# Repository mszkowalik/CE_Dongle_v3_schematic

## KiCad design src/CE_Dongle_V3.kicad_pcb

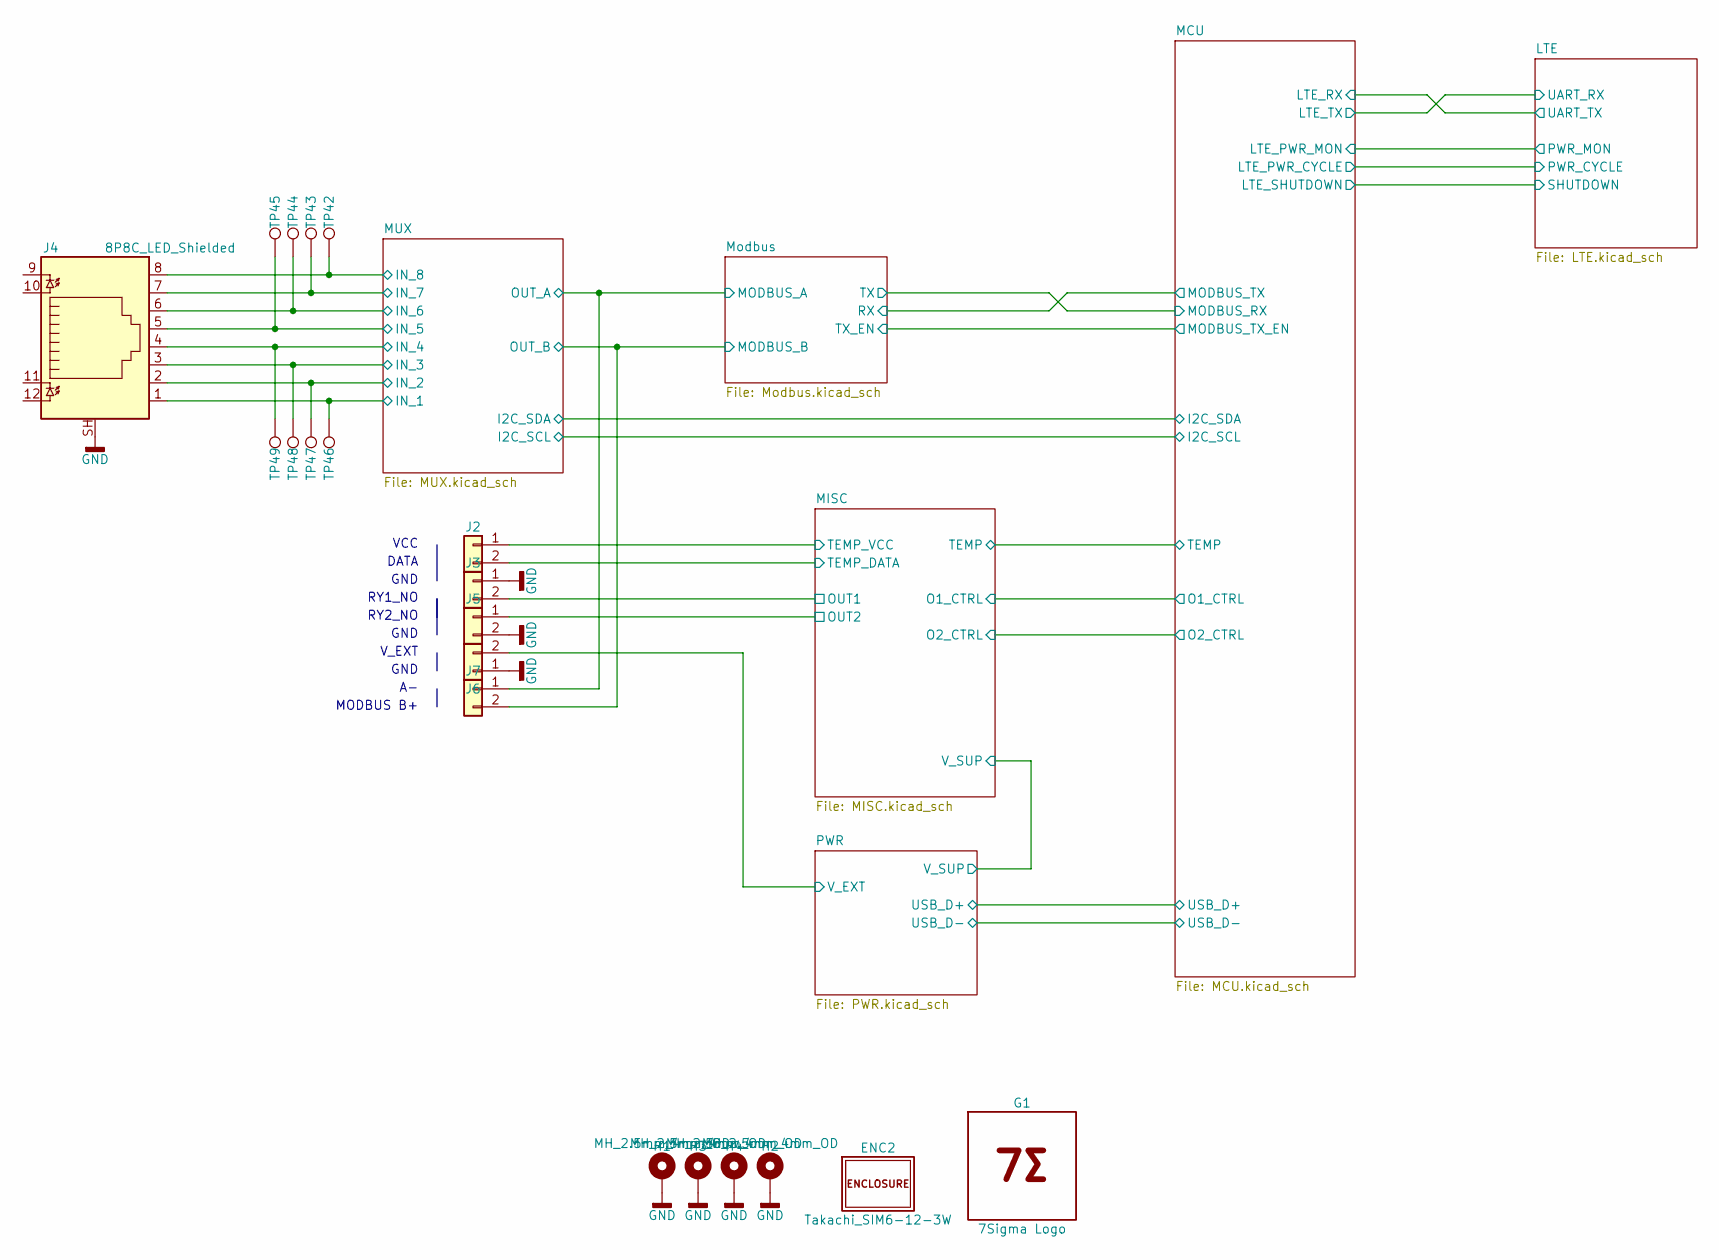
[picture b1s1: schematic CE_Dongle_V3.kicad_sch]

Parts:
ENC2: Takachi_SIM6-12-3W; TAKACHI_SIM6-12-3W; Manufacturer Part Numbe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 SIM6-12-3W
G1: 7Sigma Logo; 7Sigma_Logo
H1, H2, H3, H4: MH_2.5mm_4mm_OD; MountingHole_2.5mm_Pad_4mm
J2, J3, J5, J6, J7: Conn_01x02; CONN-TH_XY302V-3.5-2P; Manufacturer Part Numbe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 XY302V-3.5-2P; LCSC Part C784940
J4: 8P8C_LED_Shielded; RJ45-TH_RC01812; Manufacturer Part Numbe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 RC01812; LCSC Part C708645
TP42, TP43, TP44, TP45, TP46, TP47, TP48, TP49: TestPoint; TestPoint_Pad_D1.5mm

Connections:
/MISC/OUT1: J3.2; also elsewhere on the board
/MISC/OUT2: J5.1; also elsewhere on the board
/MISC/TEMP_DATA: J2.2; also elsewhere on the board
/MISC/TEMP_VCC: J2.1; also elsewhere on the board
/MUX/IN_1: J4.1, TP46.1 (1_1); also elsewhere on the board
/MUX/IN_2: J4.2, TP47.1 (1_1); also elsewhere on the board
/MUX/IN_3: J4.3, TP48.1 (1_1); also elsewhere on the board
/MUX/IN_4: J4.4, TP49.1 (1_1); also elsewhere on the board
/MUX/IN_5: J4.5, TP45.1 (1_1); also elsewhere on the board
/MUX/IN_6: J4.6, TP44.1 (1_1); also elsewhere on the board
/MUX/IN_7: J4.7, TP43.1 (1_1); also elsewhere on the board
/MUX/IN_8: J4.8, TP42.1 (1_1); also elsewhere on the board
/MUX/OUT_A: J7.1; also elsewhere on the board
/MUX/OUT_B: J7.2; also elsewhere on the board
/PWR/V_EXT: J6.2; also elsewhere on the board
GND: H1.1 (1_1), H2.1 (1_1), H3.1 (1_1), H4.1 (1_1), J3.1, J4.SH, J5.2, J6.1; also elsewhere on the board

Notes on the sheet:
VCC
GND
V_EXT
RY1_NO
DATA
MODBUS B+
RY2_NO

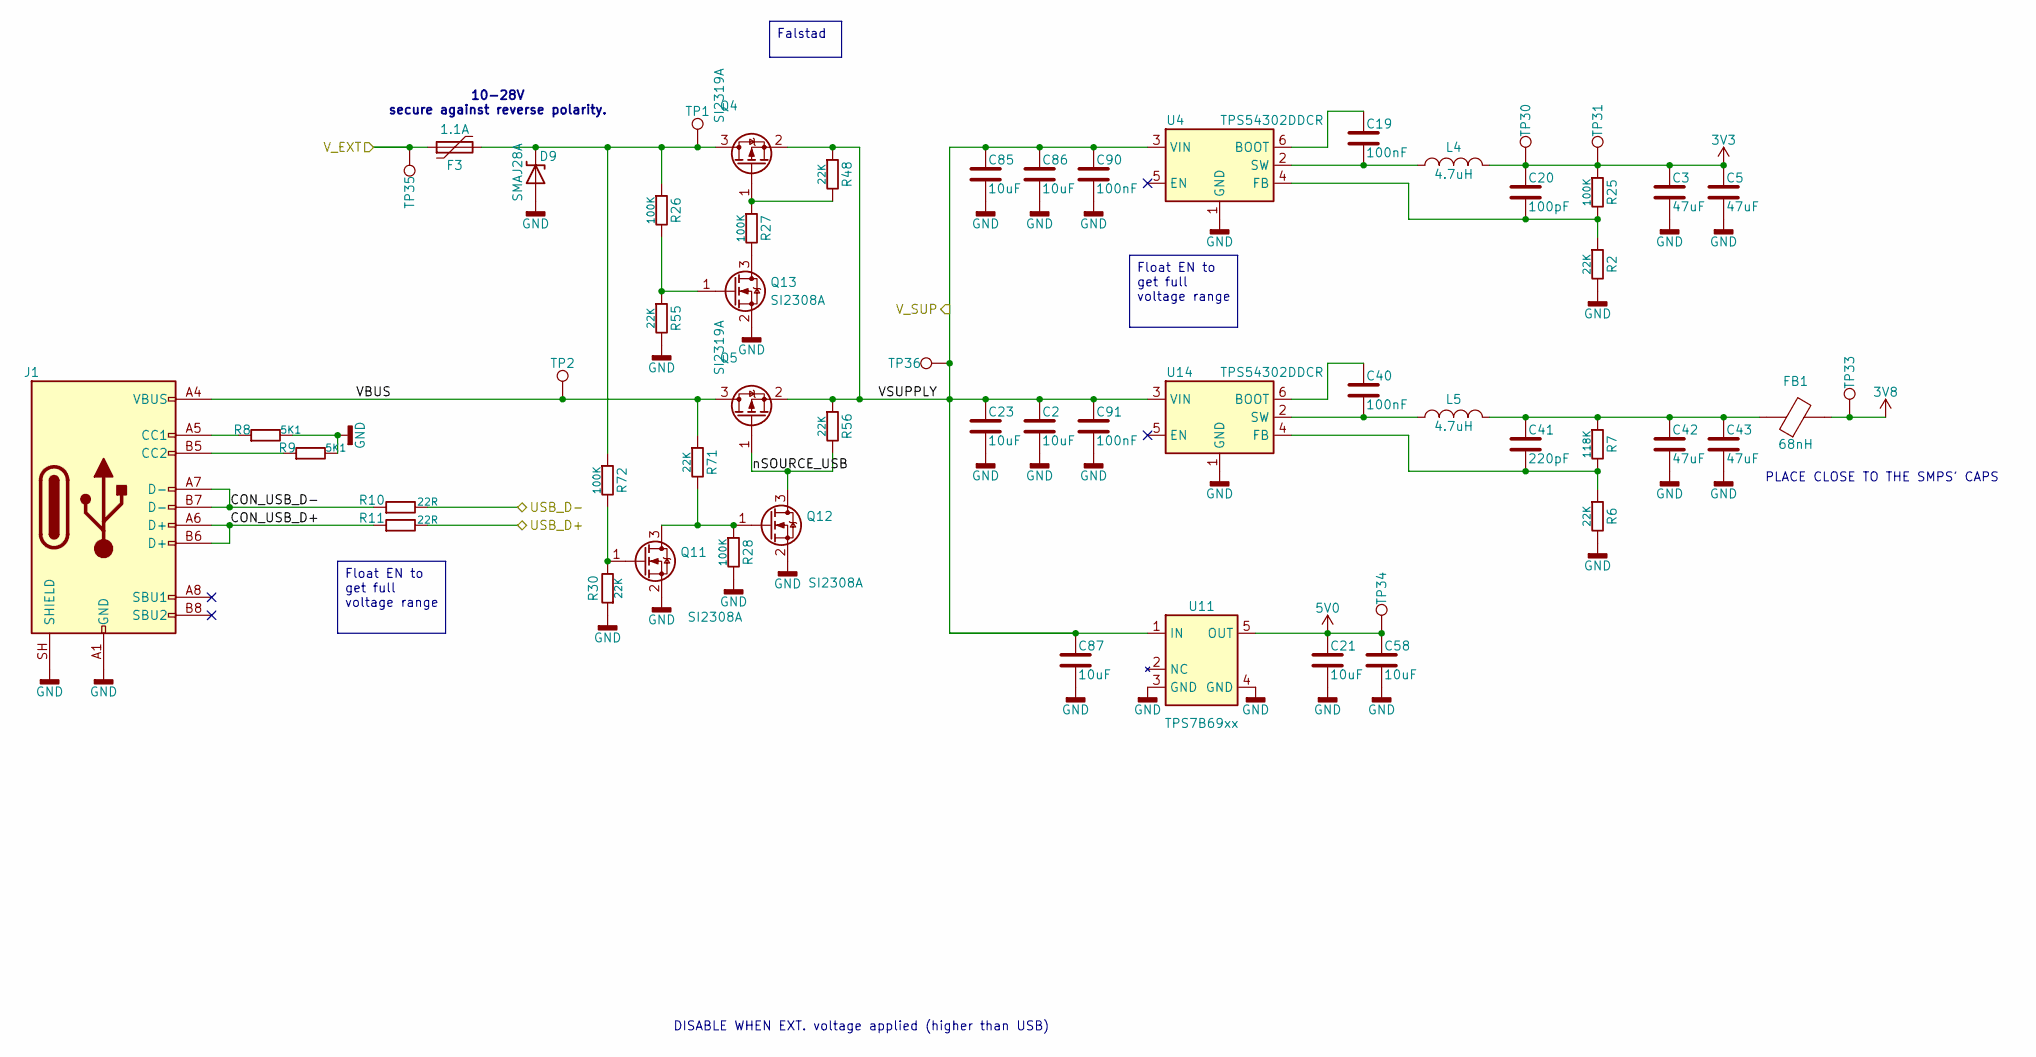
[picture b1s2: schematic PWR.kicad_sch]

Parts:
C2, C21, C23, C58, C85, C86, C87: 10uF; C_0805_2012Metric; Voltage 50V; Tolerance 10%; Manufacturer Part Numbe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 GRM21BR61H106KE43L; LCSC Part C440198
C3, C5, C42, C43: 47uF; C_1210_3225Metric; Voltage 16V; Tolerance 10%; Manufacturer Part Numbe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 CS3225X7R476K160NRL; LCSC Part C5440143
C19, C40, C90, C91: 100nF; C_0402_1005Metric; Voltage 16V; Tolerance 10%; Manufacturer Part Numbe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 CL05B104KO5NNNC; LCSC Part C1525
C20: 100pF; C_0402_1005Metric; Voltage 50V; Tolerance 5%; Manufacturer Part Numbe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 0402CG101J500NT; LCSC Part C1546
C41: 220pF; C_0402_1005Metric; Voltage 50V; Tolerance 5%; Manufacturer Part Numbe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 CC0402JRNPO9BN221; LCSC Part C107001
D9: SMAJ28A; D_SMA; Voltage - Breakdown 34.4V; Clamping Voltage 45.4V; Manufacturer Part Numbe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 SMAJ28A; LCSC Part C148227
F3: 1.1A; Fuse_1206_3216Metric; Voltage_Max 30V; Manufacturer Part Numbe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 BSMD1206-110-30V; LCSC Part C21714343
FB1: 68nH; L_0603_1608Metric; Tolerance 25%; Manufacturer Part Numbe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 BLM18EG101TN1D; LCSC Part C76893
J1: USB_C_Receptacle_USB2.0_16P; USB-3.1-SMD_U262-161N-4BVC11; Manufacturer Part Numbe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 U262-161N-4BVC11; LCSC Part C319148
L4, L5: 4.7uH; L_Changjiang_FTC404030S; Tolerance 20%; Manufacturer Part Numbe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 FTC404030S4R7MGCA; LCSC Part C39676083
Q4, Q5: SI2319A; SOT-23-3; Manufacturer Part Numbe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 SI2319A; LCSC Part C545576
Q11, Q12, Q13: SI2308A; SOT-23-3; Manufacturer Part Numbe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 SI2308A; LCSC Part C347491
R2, R6, R30, R48, R55, R56, R71: 22K; R_0402_1005Metric; Tolerance 1%; Manufacturer Part Numbe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 0402WGF2202TCE; LCSC Part C25768
R7: 118K; R_0402_1005Metric; Tolerance 1%; Manufacturer Part Numbe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 0402WGF1183TCE; LCSC Part C25748
R8, R9: 5K1; R_0402_1005Metric; Tolerance 1%; Manufacturer Part Numbe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 0402WGF5101TCE; LCSC Part C25905
R10, R11: 22R; R_0402_1005Metric; Tolerance 1%; Manufacturer Part Numbe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 0402WGF220JTCE; LCSC Part C25092
R25, R26, R27, R28, R72: 100K; R_0402_1005Metric; Tolerance 1%; Manufacturer Part Numbe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 0402WGF1003TCE; LCSC Part C25741
TP1, TP2, TP30, TP31, TP33, TP34, TP35, TP36: TestPoint; TestPoint_Pad_D1.5mm
U4, U14: TPS54302DDCR; SOT-23-6; Output Voltage Adj; Input Voltage 4.5V~28V; Manufacturer Part Numbe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 TPS54302DDCR; LCSC Part C311983
U11: TPS7B69xx; SOT-23-5; Output Voltage 5V; Dropout Voltage 450mV@(100mA); Manufacturer Part Numbe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 TPS7B6950QDBVRQ1; LCSC Part C132202

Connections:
3V3: C3.1, C5.1, C20.1, L4.2, R25.1, TP30.1 (1_1), TP31.1 (1_1); also elsewhere on the board
3V8: FB1.2, TP33.1 (1_1); also elsewhere on the board
5V0: C21.1, C58.1, TP34.1 (1_1), U11.5 (OUT); also elsewhere on the board
/MCU/USB_D+: R11.2; also elsewhere on the board
/MCU/USB_D-: R10.2; also elsewhere on the board
/MISC/VSUPPLY: C2.1, C23.1, C85.1, C86.1, C87.1, C90.1, C91.1, Q4.2 (S), Q5.2 (S), R48.1, R56.1, TP36.1 (1_1), U4.3 (VIN), U11.1 (IN), U14.3 (VIN); also elsewhere on the board
/PWR/CON_USB_D+: J1.A6 (D+), J1.B6 (D+), R11.1
/PWR/CON_USB_D-: J1.A7 (D-), J1.B7 (D-), R10.1
/PWR/VBUS: J1.A4 (VBUS), J1.A9 (VBUS), J1.B4 (VBUS), J1.B9 (VBUS), Q5.3 (D), R71.1, TP2.1 (1_1)
/PWR/V_EXT: F3.1, TP35.1 (1_1); also elsewhere on the board
/PWR/nSOURCE_USB: Q5.1 (G), Q12.3 (D), R56.2
GND: C2.2, C3.2, C5.2, C21.2, C23.2, C42.2, C43.2, C58.2, C85.2, C86.2, C87.2, C90.2, C91.2, D9.2 (A), J1.A1 (GND), J1.A12 (GND), J1.B1 (GND), J1.B12 (GND), J1.SH (SHIELD), Q11.2 (S), Q12.2 (S), Q13.2 (S), R2.2, R6.2, R8.2, R9.2, R28.2, R30.1, R55.2, U4.1 (GND), U11.3 (GND), U11.4 (GND), U14.1 (GND); also elsewhere on the board
unnamed: C41.1, C42.1, C43.1, FB1.1, L5.2, R7.1
unnamed: D9.1 (C), F3.2, Q4.3 (D), R26.1, R72.1, TP1.1 (1_1)
unnamed: J1.A5 (CC1), R8.1
unnamed: J1.B5 (CC2), R9.1
unnamed: Q4.1 (G), R27.1, R48.2
unnamed: Q11.3 (D), Q12.1 (G), R28.1, R71.2
unnamed: Q11.1 (G), R30.2, R72.2
unnamed: Q13.3 (D), R27.2
unnamed: Q13.1 (G), R26.2, R55.1
unnamed: C19.1, U4.6 (BOOT)
unnamed: C20.2, R2.1, R25.2, U4.4 (FB)
unnamed: C19.2, L4.1, U4.2 (SW)
unnamed: C40.1, U14.6 (BOOT)
unnamed: C41.2, R6.1, R7.2, U14.4 (FB)
unnamed: C40.2, L5.1, U14.2 (SW)

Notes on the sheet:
10-28V secure against reverse polarity.
DISABLE WHEN EXT. voltage applied (higher than USB)
PLACE CLOSE TO THE SMPS' CAPS
Float EN to get full voltage range
Falstad

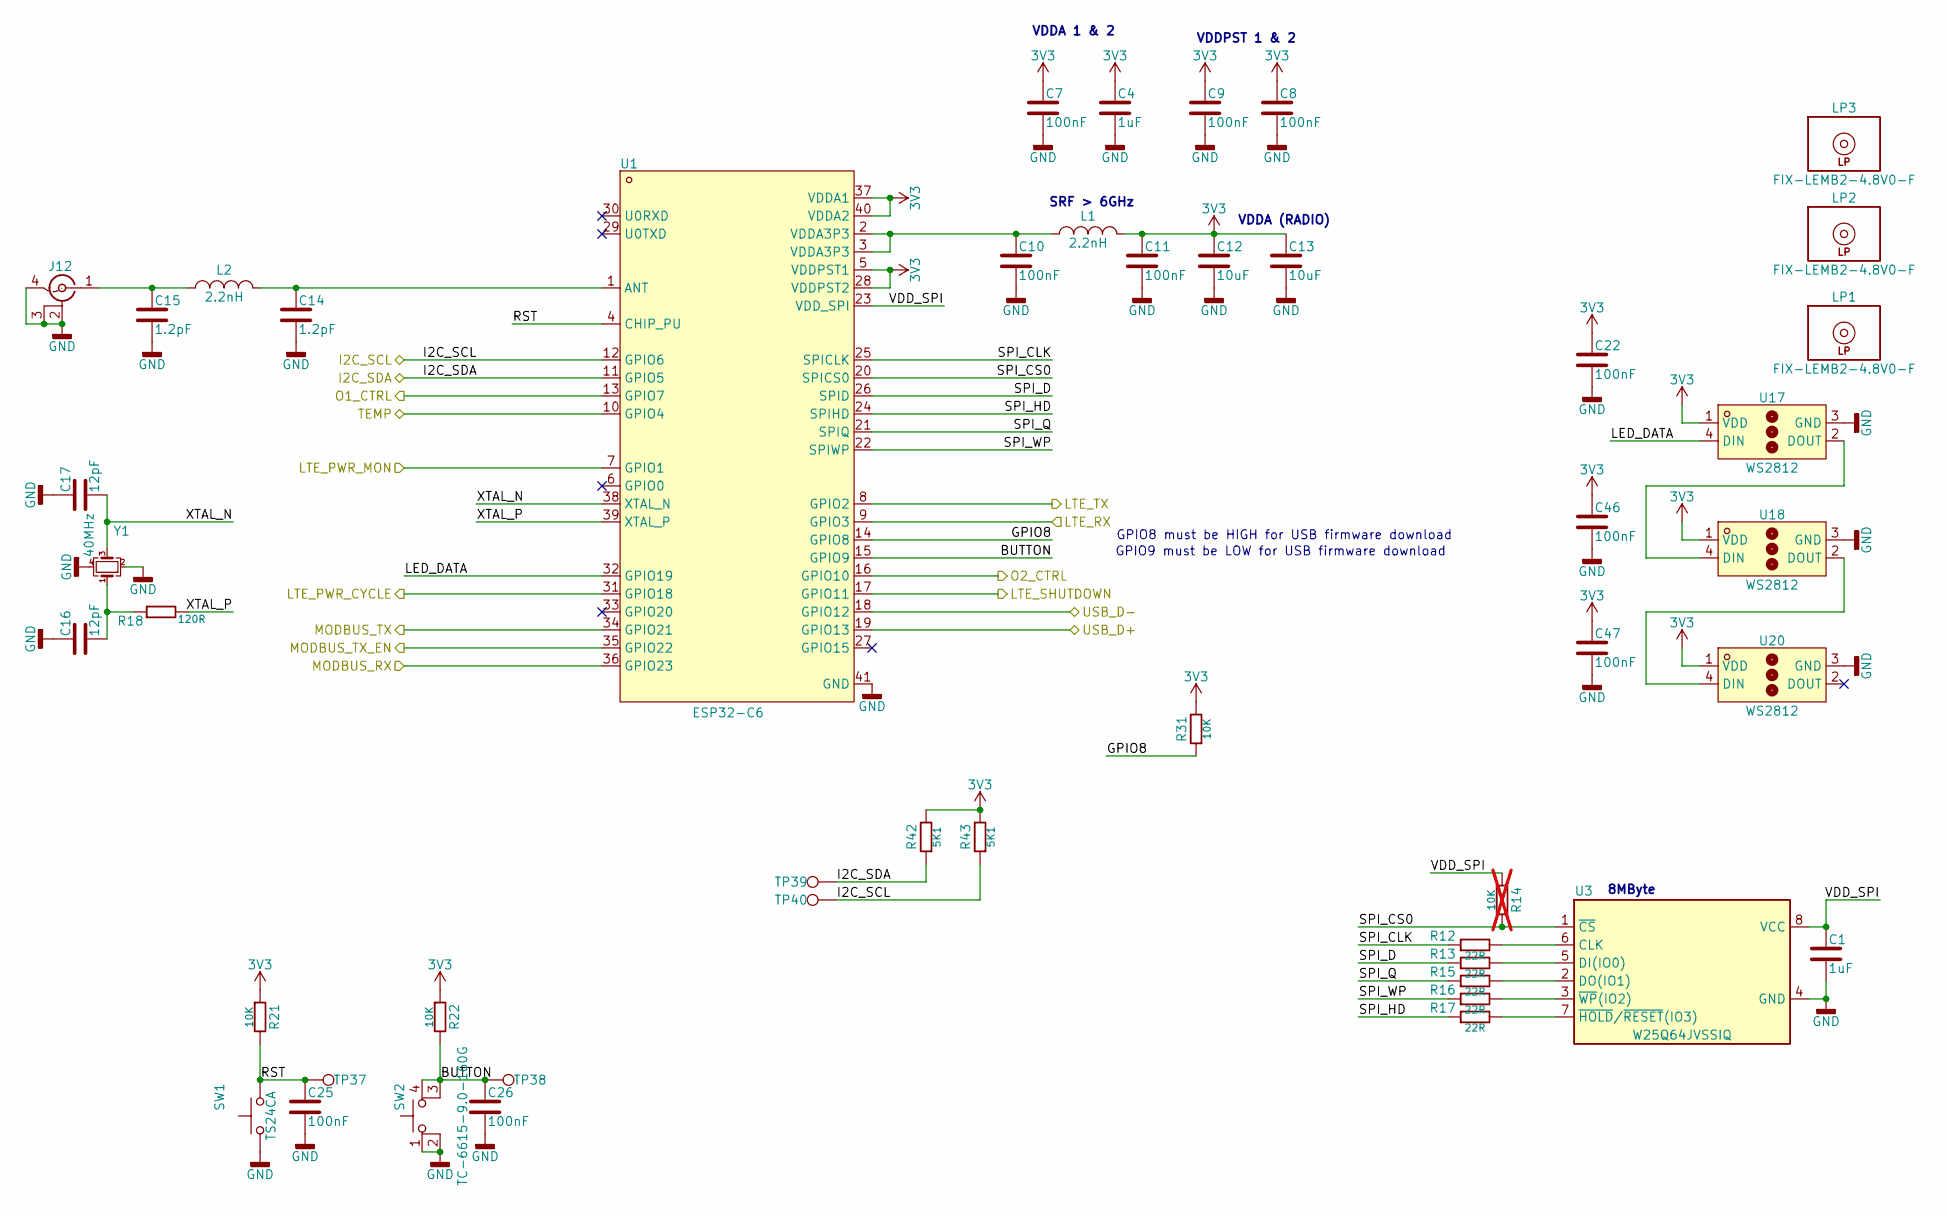
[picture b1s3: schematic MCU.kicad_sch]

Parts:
C1, C4: 1uF; C_0402_1005Metric; Voltage 50V; Tolerance 1%; Manufacturer Part Numbe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 GRM155R61H105KE05D; LCSC Part C1518208
C7, C8, C9, C10, C11, C22, C25, C26, C46, C47: 100nF; C_0402_1005Metric; Voltage 16V; Tolerance 10%; Manufacturer Part Numbe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 CL05B104KO5NNNC; LCSC Part C1525
C12, C13: 10uF; C_0402_1005Metric; Voltage 10V; Tolerance 10%; Manufacturer Part Numbe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 CL05A106MP5NUNC; LCSC Part C315248
C14, C15: 1.2pF; C_0402_1005Metric; Voltage 50V; Tolerance 0.05pF; Manufacturer Part Numbe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 GJM1555C1H1R2WB01D; LCSC Part C76899
C16, C17: 12pF; C_0402_1005Metric; Voltage 50V; Tolerance 5%; Manufacturer Part Numbe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 CC0402JRNPO9BN120; LCSC Part C106201
J12: Conn_IPEX; ANT-SMD_KH-IPEX-K501-29; Manufacturer Part Numbe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 KH-IPEX-K501-29; LCSC Part C411563
L1, L2: 2.2nH; L_0402_1005Metric; Tolerance 10%; Manufacturer Part Numbe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 LQW15AN2N2C10D; LCSC Part C91240
LP1, LP2, LP3: FIX-LEMB2-4.8V0-F; Manufacturer Part Numbe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 FIX-LEMB2-4.8V0-F
R12, R13, R15, R16, R17: 22R; R_0402_1005Metric; Tolerance 1%; Manufacturer Part Numbe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 0402WGF220JTCE; LCSC Part C25092
R14: 10K; R_0402_1005Metric; Tolerance 1%; Manufacturer Part Numbe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 0402WGF1002TCE; LCSC Part C25744; not fitted
R18: 120R; R_0402_1005Metric; Tolerance 1%; Manufacturer Part Numbe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 0402WGF1200TCE; LCSC Part C25079
R21, R22, R31: 10K; R_0402_1005Metric; Tolerance 1%; Manufacturer Part Numbe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 0402WGF1002TCE; LCSC Part C25744
R42, R43: 5K1; R_0402_1005Metric; Tolerance 1%; Manufacturer Part Numbe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 0402WGF5101TCE; LCSC Part C25905
SW1: TS24CA; SW-SMD_TS24CA; Manufacturer Part Numbe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 TS24CA; LCSC Part C393942
SW2: TC-6615-9.0-160G; SW-TH_4P-RA-L6.0-W6.0-H9.0; Manufacturer Part Numbe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 TC-6615-9.0-160G; LCSC Part C6575016
TP37, TP38, TP39, TP40: TestPoint; TestPoint_Pad_D1.5mm
U1: ESP32-C6; VQFN-40-1EP_5x5mm_P0.4mm_EP3.3x3.3mm_ThermalVias; Manufacturer Part Numbe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 ESP32-C6; LCSC Part C5364646
U3: W25Q64JVSSIQ; SOIC-8_5.3x5.3mm_P1.27mm; Voltage Range 2.7V~3.6V; Manufacturer Part Numbe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 W25Q64JVSSIQ; LCSC Part C179171
U17, U18, U20: WS2812; LED-SMD_4P-L1.3-W1.3-P0.80_WS2812E-1313; Voltage Range 3.7V~5.3V; Manufacturer Part Numbe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 WS2812E-1313; LCSC Part C5446700
Y1: 40MHz; Crystal_SMD_3225-4Pin_3.2x2.5mm; Tolerance 10ppm; Manufacturer Part Numbe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 XTM32040000FT00351001; LCSC Part C37635390

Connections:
3V3: C4.1, C7.1, C8.1, C9.1, C11.1, C12.1, C13.1, C22.1, C46.1, C47.1, L1.2, R21.1, R22.1, R31.2, R42.2, R43.2, U1.5 (VDDPST1), U1.28 (VDDPST2), U1.37 (VDDA1), U1.40 (VDDA2), U17.1 (VDD), U18.1 (VDD), U20.1 (VDD); also elsewhere on the board
/LTE/PWR_CYCLE: U1.31 (GPIO18); also elsewhere on the board
/LTE/PWR_MON: U1.7 (GPIO1); also elsewhere on the board
/LTE/SHUTDOWN: U1.17 (GPIO11); also elsewhere on the board
/LTE/UART_RX: U1.8 (GPIO2); also elsewhere on the board
/LTE/UART_TX: U1.9 (GPIO3); also elsewhere on the board
/MCU/BUTTON: C26.1, R22.2, SW2.3 (K), SW2.4 (A), TP38.1 (1_1), U1.15 (GPIO9)
/MCU/GPIO8: R31.1, U1.14 (GPIO8)
/MCU/I2C_SCL: R43.1, TP40.1 (1_1), U1.12 (GPIO6); also elsewhere on the board
/MCU/I2C_SDA: R42.1, TP39.1 (1_1), U1.11 (GPIO5); also elsewhere on the board
/MCU/LED_DATA: U1.32 (GPIO19), U17.4 (DIN)
/MCU/MODBUS_RX: U1.36 (GPIO23); also elsewhere on the board
/MCU/MODBUS_TX: U1.34 (GPIO21); also elsewhere on the board
/MCU/MODBUS_TX_EN: U1.35 (GPIO22); also elsewhere on the board
/MCU/O1_CTRL: U1.13 (GPIO7); also elsewhere on the board
/MCU/O2_CTRL: U1.16 (GPIO10); also elsewhere on the board
/MCU/RST: C25.1, R21.2, SW1.2, TP37.1 (1_1), U1.4 (CHIP_PU)
/MCU/SPI_CLK: R12.1, U1.25 (SPICLK)
/MCU/SPI_CS0: R14.2, U1.20 (SPICS0), U3.1 (~CS)
/MCU/SPI_D: R13.1, U1.26 (SPID)
/MCU/SPI_HD: R17.1, U1.24 (SPIHD)
/MCU/SPI_Q: R15.1, U1.21 (SPIQ)
/MCU/SPI_WP: R16.1, U1.22 (SPIWP)
/MCU/USB_D+: U1.19 (GPIO13); also elsewhere on the board
/MCU/USB_D-: U1.18 (GPIO12); also elsewhere on the board
/MCU/VDD_SPI: C1.1, R14.1, U1.23 (VDD_SPI), U3.8 (VCC)
/MCU/XTAL_N: C17.2, U1.38 (XTAL_N), Y1.3
/MCU/XTAL_P: R18.2, U1.39 (XTAL_P)
/MISC/TEMP: U1.10 (GPIO4); also elsewhere on the board
GND: C1.2, C4.2, C7.2, C8.2, C9.2, C10.2, C11.2, C12.2, C13.2, C14.2, C15.2, C16.1, C17.1, C22.2, C25.2, C26.2, C46.2, C47.2, J12.2 (Ext), J12.3 (Ext), J12.4 (PT), SW1.1, SW2.1, SW2.2, U1.41 (GND), U3.4 (GND), U17.3 (GND), U18.3 (GND), U20.3 (GND), Y1.2, Y1.4; also elsewhere on the board
unnamed: C10.1, L1.1, U1.2 (VDDA3P3), U1.3 (VDDA3P3)
unnamed: C16.2, R18.1, Y1.1
unnamed: C15.1, J12.1 (In), L2.1
unnamed: C14.1, L2.2, U1.1 (ANT)
unnamed: R12.2, U3.6 (CLK)
unnamed: R13.2, U3.5 (DI(IO0))
unnamed: R15.2, U3.2 (DO(IO1))
unnamed: R17.2, U3.7 (~HOLD/~RESET(IO3))
unnamed: R16.2, U3.3 (~WP(IO2))
unnamed: U17.2 (DOUT), U18.4 (DIN)
unnamed: U18.2 (DOUT), U20.4 (DIN)

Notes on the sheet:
VDDA (RADIO)
SRF > 6GHz
GPIO8 must be HIGH for USB firmware download
VDDA 1 & 2
8MByte
VDDPST 1 & 2
GPIO9 must be LOW for USB firmware download

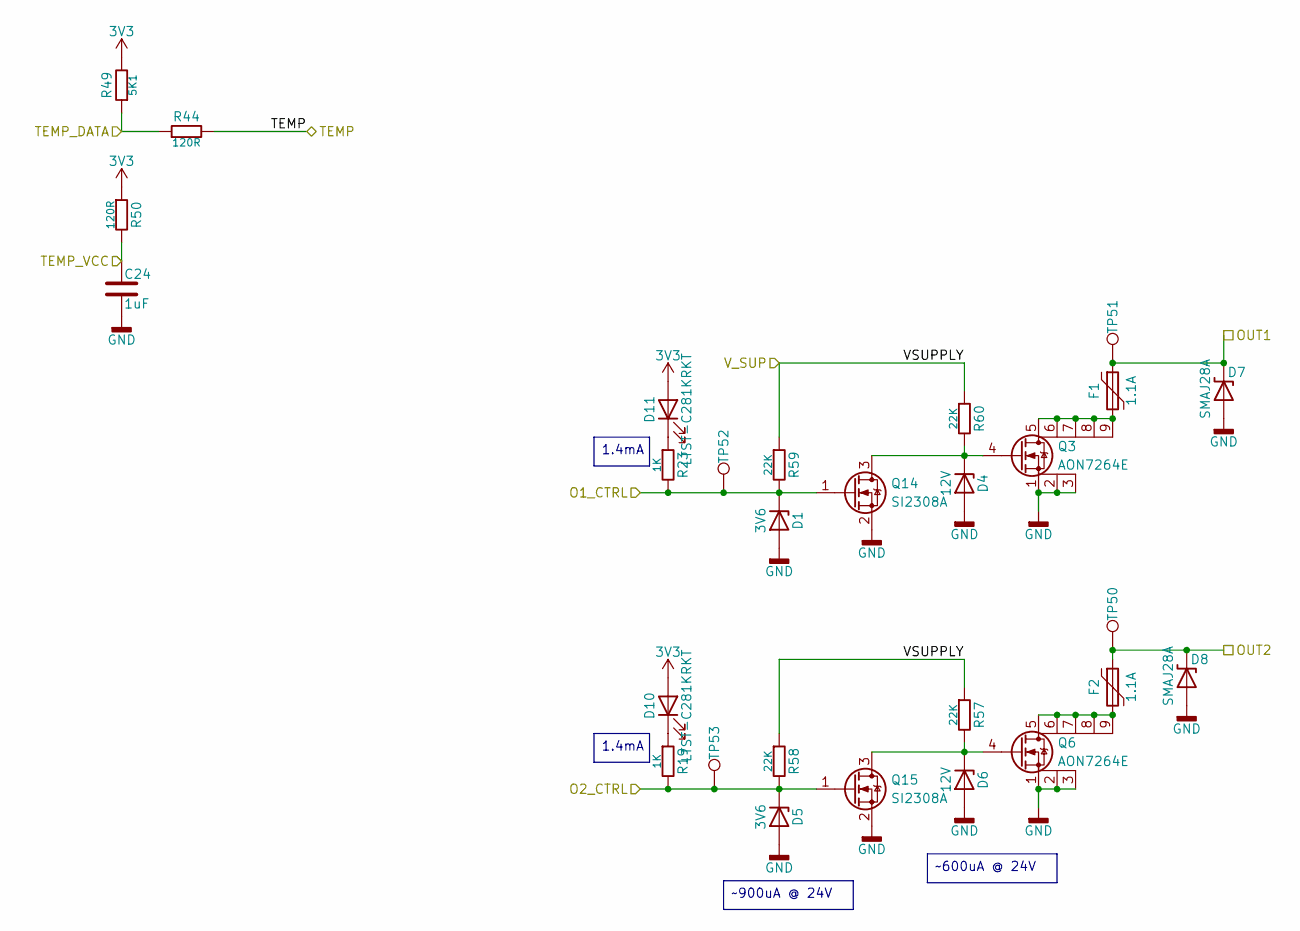
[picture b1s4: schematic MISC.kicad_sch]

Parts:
C24: 1uF; C_0402_1005Metric; Voltage 50V; Tolerance 1%; Manufacturer Part Numbe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 GRM155R61H105KE05D; LCSC Part C1518208
D1, D5: 3V6; D_SOD-323; Zenner Voltage 3.6V; Tolerance 5%; Manufacturer Part Numbe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 BZX384-C3V6,115; LCSC Part C454986
D4, D6: 12V; D_SOD-323; Zenner Voltage 12V; Tolerance 5%; Manufacturer Part Numbe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 BZX384-C12,115; LCSC Part C454968
D7, D8: SMAJ28A; D_SMA; Voltage - Breakdown 34.4V; Clamping Voltage 45.4V; Manufacturer Part Numbe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 SMAJ28A; LCSC Part C148227
D10, D11: LTST-C281KRKT; LED_0402_1005Metric; Forward Voltage 2V; Manufacturer Part Numbe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 LTST-C281KRKT; LCSC Part C364556
F1, F2: 1.1A; Fuse_1206_3216Metric; Voltage_Max 30V; Manufacturer Part Numbe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 BSMD1206-110-30V; LCSC Part C21714343
Q3, Q6: AON7264E; DFN-8-1EP_3x3mm_P0.65mm_EP1.55x2.4mm; Manufacturer Part Numbe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 AON7264E; LCSC Part C431191
Q14, Q15: SI2308A; SOT-23-3; Manufacturer Part Numbe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 SI2308A; LCSC Part C347491
R19, R23: 1K; R_0402_1005Metric; Tolerance 1%; Manufacturer Part Numbe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 0402WGF1001TCE; LCSC Part C11702
R44: 120R; R_0402_1005Metric; Tolerance 1%; Manufacturer Part Numbe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 0402WGF1200TCE; LCSC Part C25079
R49: 5K1; R_0402_1005Metric; Tolerance 1%; Manufacturer Part Numbe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 0402WGF5101TCE; LCSC Part C25905
R50: 120R; R_0805_2012Metric; Tolerance 1%; Manufacturer Part Numbe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 0805W8F1200T5E; LCSC Part C17437
R57, R58, R59, R60: 22K; R_0402_1005Metric; Tolerance 1%; Manufacturer Part Numbe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 0402WGF2202TCE; LCSC Part C25768
TP50, TP51, TP52, TP53: TestPoint; TestPoint_Pad_D1.5mm

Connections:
3V3: D10.2 (A), D11.2 (A), R49.2, R50.1; also elsewhere on the board
/MCU/O1_CTRL: D1.1 (K), Q14.1 (G), R23.2, R59.2, TP52.1 (1_1); also elsewhere on the board
/MCU/O2_CTRL: D5.1 (K), Q15.1 (G), R19.2, R58.2, TP53.1 (1_1); also elsewhere on the board
/MISC/OUT1: D7.1 (C), F1.1, TP51.1 (1_1); also elsewhere on the board
/MISC/OUT2: D8.1 (C), F2.1, TP50.1 (1_1); also elsewhere on the board
/MISC/TEMP: R44.2; also elsewhere on the board
/MISC/TEMP_DATA: R44.1, R49.1; also elsewhere on the board
/MISC/TEMP_VCC: C24.1, R50.2; also elsewhere on the board
/MISC/VSUPPLY: R57.1, R58.1, R59.1, R60.1; also elsewhere on the board
GND: C24.2, D1.2 (A), D4.2 (A), D5.2 (A), D6.2 (A), D7.2 (A), D8.2 (A), Q3.1 (S), Q3.2 (S), Q3.3 (S), Q6.1 (S), Q6.2 (S), Q6.3 (S), Q14.2 (S), Q15.2 (S); also elsewhere on the board
unnamed: D4.1 (K), Q3.4 (G), Q14.3 (D), R60.2
unnamed: D6.1 (K), Q6.4 (G), Q15.3 (D), R57.2
unnamed: D10.1 (K), R19.1
unnamed: D11.1 (K), R23.1
unnamed: F1.2, Q3.5 (D), Q3.6 (D), Q3.7 (D), Q3.8 (D), Q3.9 (D)
unnamed: F2.2, Q6.5 (D), Q6.6 (D), Q6.7 (D), Q6.8 (D), Q6.9 (D)

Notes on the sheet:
~600uA @ 24V
1.4mA
~900uA @ 24V

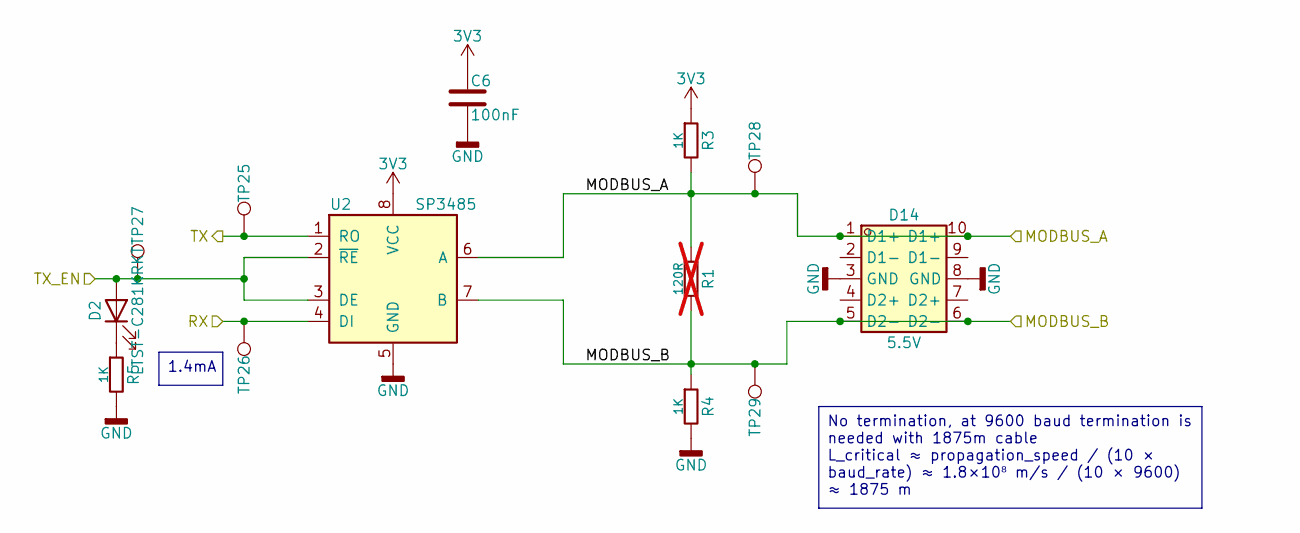
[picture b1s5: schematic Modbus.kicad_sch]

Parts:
C6: 100nF; C_0402_1005Metric; Voltage 16V; Tolerance 10%; Manufacturer Part Numbe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 CL05B104KO5NNNC; LCSC Part C1525
D2: LTST-C281KRKT; LED_0402_1005Metric; Forward Voltage 2V; Manufacturer Part Numbe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 LTST-C281KRKT; LCSC Part C364556
D14: 5.5V; USON-10_2.5x1.0mm_P0.5mm; Voltage - Breakdown 6.5V; LCSC Part C138714
R1: 120R; R_0402_1005Metric; Tolerance 1%; Manufacturer Part Numbe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 0402WGF1200TCE; LCSC Part C25079; not fitted
R3, R4, R5: 1K; R_0402_1005Metric; Tolerance 1%; Manufacturer Part Numbe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 0402WGF1001TCE; LCSC Part C11702
TP25, TP26, TP27, TP28, TP29: TestPoint; TestPoint_Pad_D1.5mm
U2: SP3485; SOIC-8_3.9x4.9mm_P1.27mm; Manufacturer Part Numbe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 SP3485EN-L/TR; LCSC Part C8963

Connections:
3V3: C6.1, R3.1, U2.8 (VCC); also elsewhere on the board
/MCU/MODBUS_RX: TP25.1 (1_1), U2.1 (RO); also elsewhere on the board
/MCU/MODBUS_TX: TP26.1 (1_1), U2.4 (DI); also elsewhere on the board
/MCU/MODBUS_TX_EN: D2.2 (A), TP27.1 (1_1), U2.2 (~RE), U2.3 (DE); also elsewhere on the board
/MUX/OUT_A: D14.1 (D1+), D14.10 (D1+), R1.1, R3.2, TP28.1 (1_1), U2.6 (A); also elsewhere on the board
/MUX/OUT_B: D14.5 (D2-), D14.6 (D2-), R1.2, R4.1, TP29.1 (1_1), U2.7 (B); also elsewhere on the board
GND: C6.2, D14.3 (GND), D14.8 (GND), R4.2, R5.2, U2.5 (GND); also elsewhere on the board
unnamed: D2.1 (K), R5.1

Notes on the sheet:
1.4mA
No termination, at 9600 baud termination is needed with 1875m cable L_critical ≈ propagation_speed / (10 × baud_rate) ≈ 1.8×10⁸ m/s / (10 × 9600) ≈ 1875 m

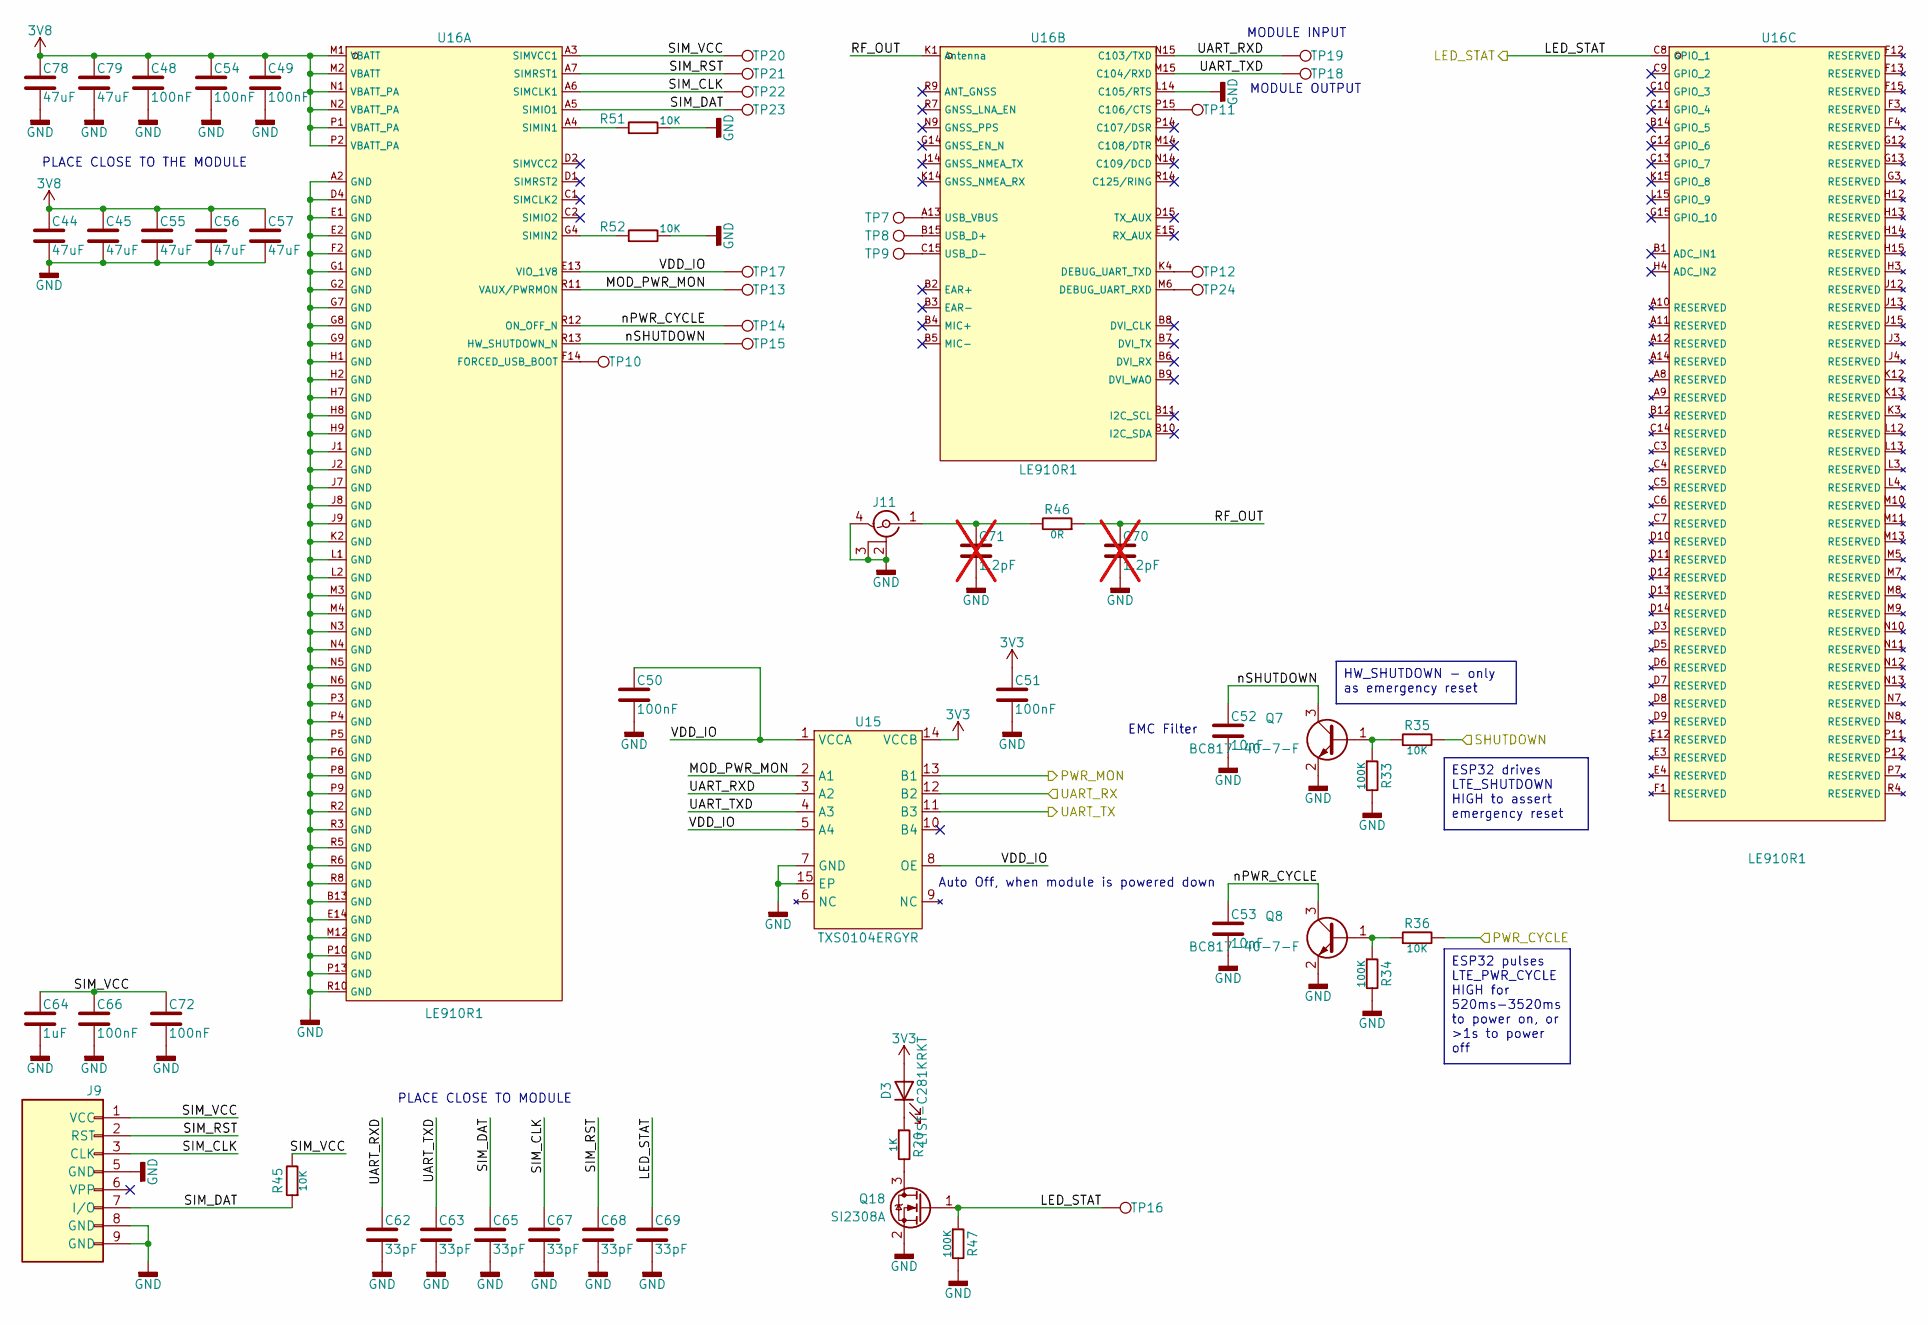
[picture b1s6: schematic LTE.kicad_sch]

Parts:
C44, C45, C55, C56, C57, C78, C79: 47uF; C_1210_3225Metric; Voltage 16V; Tolerance 10%; Manufacturer Part Numbe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 CS3225X7R476K160NRL; LCSC Part C5440143
C48, C49, C50, C51, C54, C66, C72: 100nF; C_0402_1005Metric; Voltage 16V; Tolerance 10%; Manufacturer Part Numbe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 CL05B104KO5NNNC; LCSC Part C1525
C52, C53: 10nF; C_0402_1005Metric; Voltage 50V; Tolerance 10%; Manufacturer Part Numbe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 CL05B103KB5NNNC; LCSC Part C15195
C62, C63, C65, C67, C68, C69: 33pF; C_0402_1005Metric; Voltage 50V; Tolerance 5%; Manufacturer Part Numbe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 CC0402JRNPO9BN330; LCSC Part C107005
C64: 1uF; C_0402_1005Metric; Voltage 50V; Tolerance 1%; Manufacturer Part Numbe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 GRM155R61H105KE05D; LCSC Part C1518208
C70, C71: 1.2pF; C_0402_1005Metric; Voltage 50V; Tolerance 0.05pF; Manufacturer Part Numbe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 GJM1555C1H1R2WB01D; LCSC Part C76899; not fitted
D3: LTST-C281KRKT; LED_0402_1005Metric; Forward Voltage 2V; Manufacturer Part Numbe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 LTST-C281KRKT; LCSC Part C364556
J9: SIM_NANO_Socket; SIM-SMD_NANO-SIM-TL6P-H1.35; Manufacturer Part Numbe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 NANO SIM TL6P H1.35; LCSC Part C7529385
J11: Conn_IPEX; ANT-SMD_KH-IPEX-K501-29; Manufacturer Part Numbe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 KH-IPEX-K501-29; LCSC Part C411563
Q7, Q8: BC817-40-7-F; SOT-23-3; Manufacturer Part Numbe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 BC817-40-7-F; LCSC Part C435867
Q18: SI2308A; SOT-23-3; Manufacturer Part Numbe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 SI2308A; LCSC Part C347491
R20: 1K; R_0402_1005Metric; Tolerance 1%; Manufacturer Part Numbe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 0402WGF1001TCE; LCSC Part C11702
R33, R34, R47: 100K; R_0402_1005Metric; Tolerance 1%; Manufacturer Part Numbe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 0402WGF1003TCE; LCSC Part C25741
R35, R36, R45, R51, R52: 10K; R_0402_1005Metric; Tolerance 1%; Manufacturer Part Numbe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 0402WGF1002TCE; LCSC Part C25744
R46: 0R; R_0402_1005Metric; Tolerance 1%; Manufacturer Part Numbe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 0402WGF0000TCE; LCSC Part C17168
TP7, TP8, TP9, TP10, TP11, TP12, TP13, TP14, TP15, TP16, TP17, TP18, TP19, TP20, TP21, TP22, TP23, TP24: TestPoint; TestPoint_Pad_D1.5mm
U15: TXS0104ERGYR; VQFN-14_L3.5-W3.5-P0.50-BL-EP-ThermalVias; Manufacturer Part Numbe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 TXS0104ERGYR; LCSC Part C154926
U16: LE910R1; XCVR_LE910R1-EU; Manufacturer Part Numbe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 LE910R1-EU

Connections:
3V3: C51.1, D3.2 (A), U15.14 (VCCB); also elsewhere on the board
3V8: C44.1, C45.1, C48.1, C49.1, C54.1, C55.1, C56.1, C57.1, C78.1, C79.1, U16.M1 (VBATT), U16.M2 (VBATT), U16.N1 (VBATT_PA), U16.N2 (VBATT_PA), U16.P1 (VBATT_PA), U16.P2 (VBATT_PA); also elsewhere on the board
/LTE/LED_STAT: C69.1, Q18.1 (G), R47.1, TP16.1 (1_1), U16.C8 (GPIO_1)
/LTE/MOD_PWR_MON: TP13.1 (1_1), U15.2 (A1), U16.R11 (VAUX/PWRMON)
/LTE/PWR_CYCLE: R36.2; also elsewhere on the board
/LTE/PWR_MON: U15.13 (B1); also elsewhere on the board
/LTE/RF_OUT: C70.1, R46.1, U16.K1 (Antenna)
/LTE/SHUTDOWN: R35.2; also elsewhere on the board
/LTE/SIM_CLK: C67.1, J9.3 (CLK), TP22.1 (1_1), U16.A6 (SIMCLK1)
/LTE/SIM_DAT: C65.1, J9.7 (I/O), R45.1, TP23.1 (1_1), U16.A5 (SIMIO1)
/LTE/SIM_RST: C68.1, J9.2 (RST), TP21.1 (1_1), U16.A7 (SIMRST1)
/LTE/SIM_VCC: C64.1, C66.1, C72.1, J9.1 (VCC), R45.2, TP20.1 (1_1), U16.A3 (SIMVCC1)
/LTE/UART_RX: U15.12 (B2); also elsewhere on the board
/LTE/UART_RXD: C62.1, TP19.1 (1_1), U15.3 (A2), U16.N15 (C103/TXD)
/LTE/UART_TX: U15.11 (B3); also elsewhere on the board
/LTE/UART_TXD: C63.1, TP18.1 (1_1), U15.4 (A3), U16.M15 (C104/RXD)
/LTE/VDD_IO: C50.1, TP17.1 (1_1), U15.1 (VCCA), U15.5 (A4), U15.8 (OE), U16.E13 (VIO_1V8)
/LTE/nPWR_CYCLE: C53.1, Q8.3 (C), TP14.1 (1_1), U16.R12 (ON_OFF_N)
/LTE/nSHUTDOWN: C52.1, Q7.3 (C), TP15.1 (1_1), U16.R13 (HW_SHUTDOWN_N)
GND: C44.2, C45.2, C48.2, C49.2, C50.2, C51.2, C52.2, C53.2, C54.2, C55.2, C56.2, C57.2, C62.2, C63.2, C64.2, C65.2, C66.2, C67.2, C68.2, C69.2, C70.2, C71.2, C72.2, C78.2, C79.2, J9.5 (GND), J9.8 (GND), J9.9 (GND), J11.2 (Ext), J11.3 (Ext), J11.4 (PT), Q7.2 (E), Q8.2 (E), Q18.2 (S), R33.2, R34.2, R47.2, R51.2, R52.2, U15.7 (GND), U15.15 (EP), U16.A2 (GND), U16.B13 (GND), U16.D4 (GND), U16.E1 (GND), U16.E2 (GND), U16.E14 (GND), U16.F2 (GND), U16.G1 (GND), U16.G2 (GND), U16.G7 (GND), U16.G8 (GND), U16.G9 (GND), U16.H1 (GND), U16.H2 (GND), U16.H7 (GND), U16.H8 (GND), U16.H9 (GND), U16.J1 (GND), U16.J2 (GND), U16.J7 (GND), U16.J8 (GND), U16.J9 (GND), U16.K2 (GND), U16.L1 (GND), U16.L2 (GND), U16.L14 (C105/RTS), U16.M3 (GND), U16.M4 (GND), U16.M12 (GND), U16.N3 (GND), U16.N4 (GND), U16.N5 (GND), U16.N6 (GND), U16.P3 (GND), U16.P4 (GND), U16.P5 (GND), U16.P6 (GND), U16.P8 (GND), U16.P9 (GND), U16.P10 (GND), U16.P13 (GND), U16.R2 (GND), U16.R3 (GND), U16.R5 (GND), U16.R6 (GND), U16.R8 (GND), U16.R10 (GND); also elsewhere on the board
unnamed: D3.1 (K), R20.1
unnamed: C71.1, J11.1 (In), R46.2
unnamed: Q7.1 (B), R33.1, R35.1
unnamed: Q8.1 (B), R34.1, R36.1
unnamed: Q18.3 (D), R20.2
unnamed: TP10.1 (1_1), U16.F14 (FORCED_USB_BOOT)
unnamed: R51.1, U16.A4 (SIMIN1)
unnamed: R52.1, U16.G4 (SIMIN2)
unnamed: TP11.1 (1_1), U16.P15 (C106/CTS)
unnamed: TP24.1 (1_1), U16.M6 (DEBUG_UART_RXD)
unnamed: TP12.1 (1_1), U16.K4 (DEBUG_UART_TXD)
unnamed: TP8.1 (1_1), U16.B15 (USB_D+)
unnamed: TP9.1 (1_1), U16.C15 (USB_D-)
unnamed: TP7.1 (1_1), U16.A13 (USB_VBUS)

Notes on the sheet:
Auto Off, when module is powered down
MODULE INPUT
PLACE CLOSE TO MODULE
PLACE CLOSE TO THE MODULE
MODULE OUTPUT
EMC Filter
ESP32 drives LTE_SHUTDOWN HIGH to assert emergency reset
HW_SHUTDOWN - only as emergency reset
ESP32 pulses LTE_PWR_CYCLE HIGH for 520ms-3520ms to power on, or >1s to power off
